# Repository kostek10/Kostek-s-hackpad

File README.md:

# Kostek-s-hackpad
Kostek's hackpad is my first hackpad, i really  like the design and i hope to make even better projects in the future.

# CAD

# PCB

## Firmware features
made using [QMK](https://qmk.fm/)
- Encoder changes the volume
- The OLED shows "KostekPad" and base layer

## BOM:
Here are all the parts needed for assembly:

- 5x Cherry MX Switches
- 5x DSA Keycaps
- 4x M3x16mm screws
- 4x M3x5mx4mm heatset inserts.
- 1x 0.91" 128x32 OLED Display
- 1x EC11 Rotary Encoder
- 1x XIAO RP2040
- 1x Case (bottom & top)

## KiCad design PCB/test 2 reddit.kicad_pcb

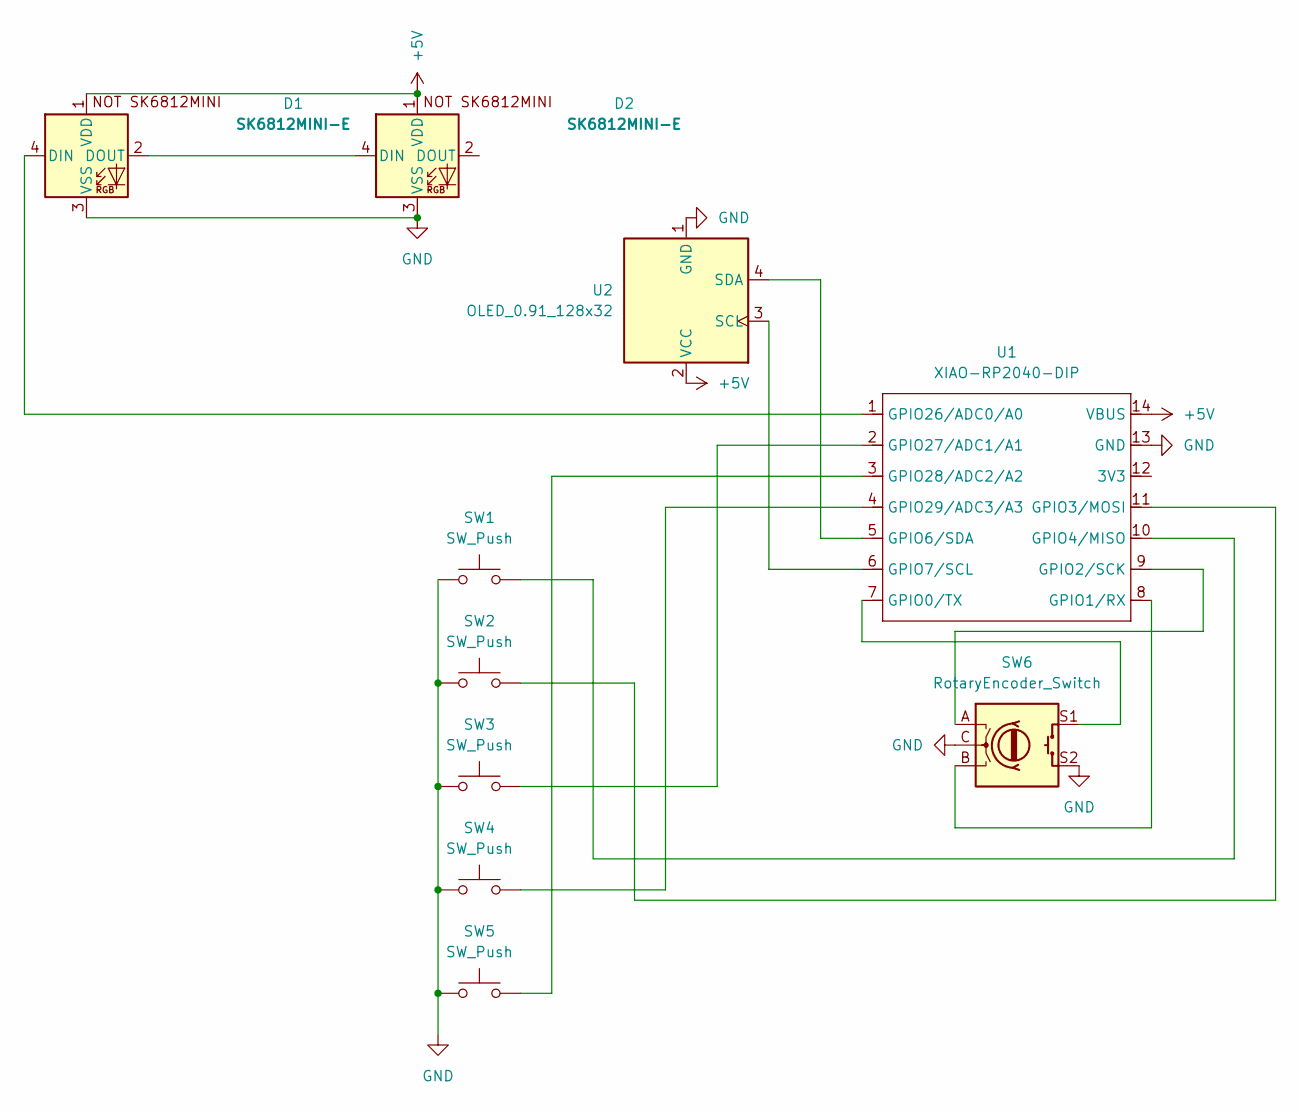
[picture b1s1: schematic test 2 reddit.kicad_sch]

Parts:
D1, D2: SK6812MINI-E; MX_SK6812MINI-E_REV
SW1, SW2, SW3, SW4, SW5: SW_Push; SW_Cherry_MX_1.00u_PCB
SW6: RotaryEncoder_Switch; RotaryEncoder_Alps_EC11E-Switch_Vertical_H20mm
U1: XIAO-RP2040-DIP
U2: OLED_0.91_128x32

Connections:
+5V: D1.1 (VDD), D2.1 (VDD), U1.14 (VBUS), U2.2 (VCC)
GND: D1.3 (VSS), D2.3 (VSS), SW1.1, SW2.1, SW3.1, SW4.1, SW5.1, SW6.C, SW6.S2, U1.13 (GND), U2.1 (GND)
unnamed: D1.4 (DIN), U1.1 (GPIO26/ADC0/A0)
unnamed: D1.2 (DOUT), D2.4 (DIN)
unnamed: SW6.S1, U1.7 (GPIO0/TX)
unnamed: SW6.B, U1.8 (GPIO1/RX)
unnamed: SW6.A, U1.9 (GPIO2/SCK)
unnamed: SW2.2, U1.11 (GPIO3/MOSI)
unnamed: SW1.2, U1.10 (GPIO4/MISO)
unnamed: U1.5 (GPIO6/SDA), U2.4 (SDA)
unnamed: U1.6 (GPIO7/SCL), U2.3 (SCL)
unnamed: SW3.2, U1.2 (GPIO27/ADC1/A1)
unnamed: SW5.2, U1.3 (GPIO28/ADC2/A2)
unnamed: SW4.2, U1.4 (GPIO29/ADC3/A3)

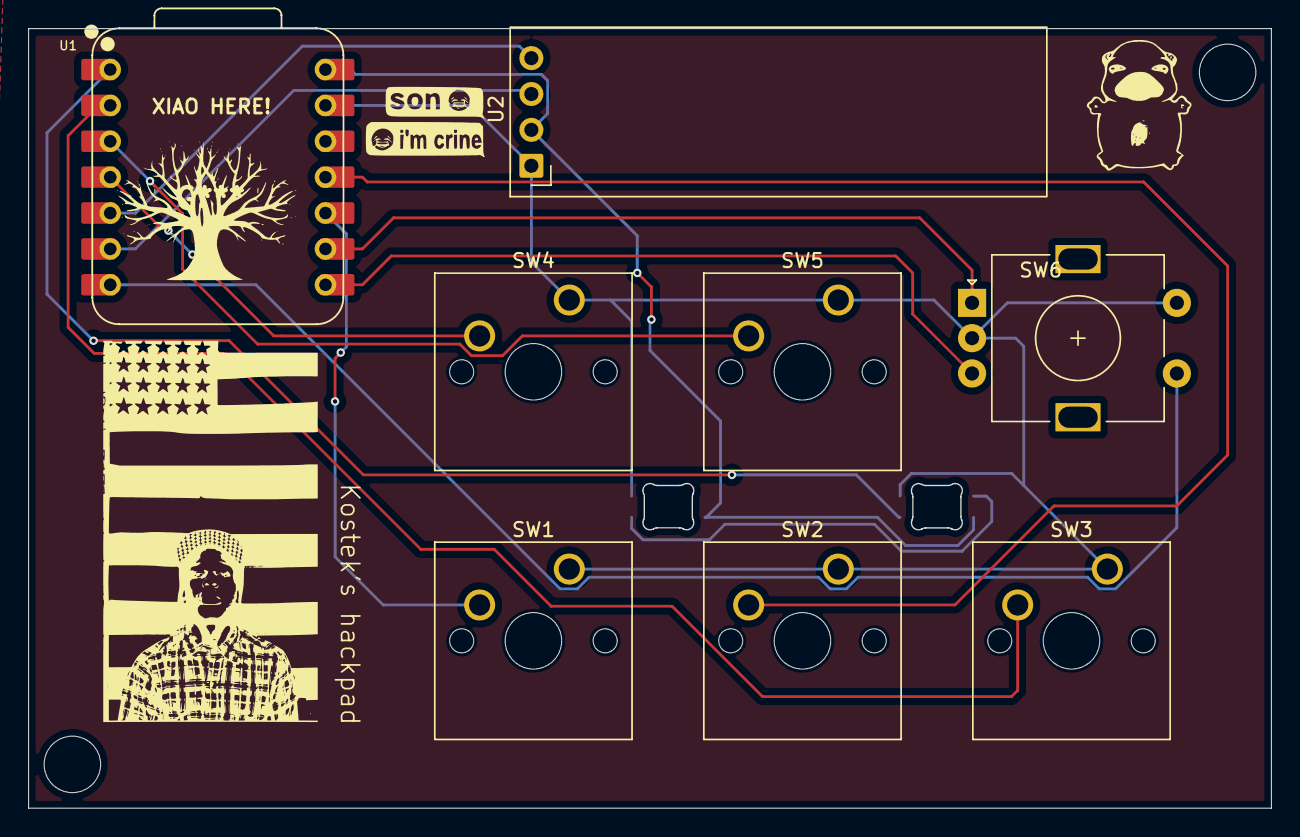
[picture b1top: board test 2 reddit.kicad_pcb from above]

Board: 2 copper layers, 88.0 x 55.2 mm, 10 parts (0 on the bottom side), 14 nets.

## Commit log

2026-01-18 Update README with project file structure
    Added file structure and image references to README.
2026-03-29 Enhance README with project details and images
    Expanded the README with detailed project information, including CAD, PCB, firmware features, and BOM.
2026-03-29 Update case description in README
